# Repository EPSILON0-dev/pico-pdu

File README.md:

# pico-pdu

Power Distribution Unit (PDU) built around the Raspberry Pi **RP2350B** (Pico 2 class MCU).

| | |
|-|-|
|  |  | |

> Status: `v0.1` prototype / work in progress. The firmware won't be finished until the board gets manufactured and tested.

## Features

* 12 channels switched with high-side MOSFETs (8 with current sensing)
* 12 PIO-based UART log collectors, aggregating over USB-CDC
* USB-CDC shell for controlling the switches and log collectors

## Hardware (pcb/)

The board is built around the RP2350B with an external flash chip. The high-side switches are controlled by the MCP23017 I2C GPIO expander. Communication is performed over USB via a USB-C port.

### Current sensing

In the current sensing channels the power is routed via a shunt resistor, whose voltage drop is amplified by the INA4180 and goes to the MCU ADCs.

### Warm Boot

A "warm boot" line is routed from the expander to the MCU; it gets pulled high after the MCU boots up. If the line is high during the MCU boot, it assumes the expander to be the source of truth and reads the GPIO states from it.

### Log Collectors

The 12 log collector channels are routed through resistors and Zener diodes to the MCU and are read with PIO UART RX blocks.

## Firmware (firmware/)

The firmware runs on FreeRTOS using one core. The firmware exposes two USB CDC interfaces **PDU Console** and **Log Collector**.

## PDU Console

For controlling and monitoring the state of the PDU.

## Log Collector (not yet implemented)

Aggregated outputs of each UART. Incoming streams are prefixed with the stream index.

### Console commands

Connect to `PDU Console` at 115200 (e.g. `picocom /dev/ttyACM0`), prompt `pico-pdu> `:

```
help                        Print help
dfu                         Enter the bootloader
relay <on|off> <channel>    Turn on/off relay channel
state                       Human-readable relay + current report
state_raw                   Machine-parseable RELAY/MONITOR dump
log                         Change logger settings (stub)
```

## Build / flash

Requires Pico SDK + ARM toolchain (easiest: Pico VS Code extension, which picks up `pico-vscode.cmake` automatically).

```sh
cd firmware
cmake -B build
cmake --build build
# produces build/pico_pdu.uf2
```

Flash: hold `USB_Boot` + tap `Reset`, copy `pico_pdu.uf2` to the mass-storage device — or run `dfu` from the console (`reset_usb_boot(0,0)`), or use Picotool/OpenOCD via SWD.

## TODOs

- `relay_init/on/off` is in-RAM only, no GPIO/expander wiring.
- `monitor_read_channel_microamps()` returns random data; needs ADC/INA4180 bring-up.
- `cmd_logger` / `LOGGER` output unimplemented.
- `pico_pdu.c` demo only services one RX channel (`piouart0`); multi-channel RX + `NUM_LOGGERS=12` mapping TBD.
- Small bug surface: `send_circular_buffer()` wrap math, `console_command()` extra `\r\n`, `relay` channel bounds message (`0-NUM_RELAYS-1` vs `<=0` check).

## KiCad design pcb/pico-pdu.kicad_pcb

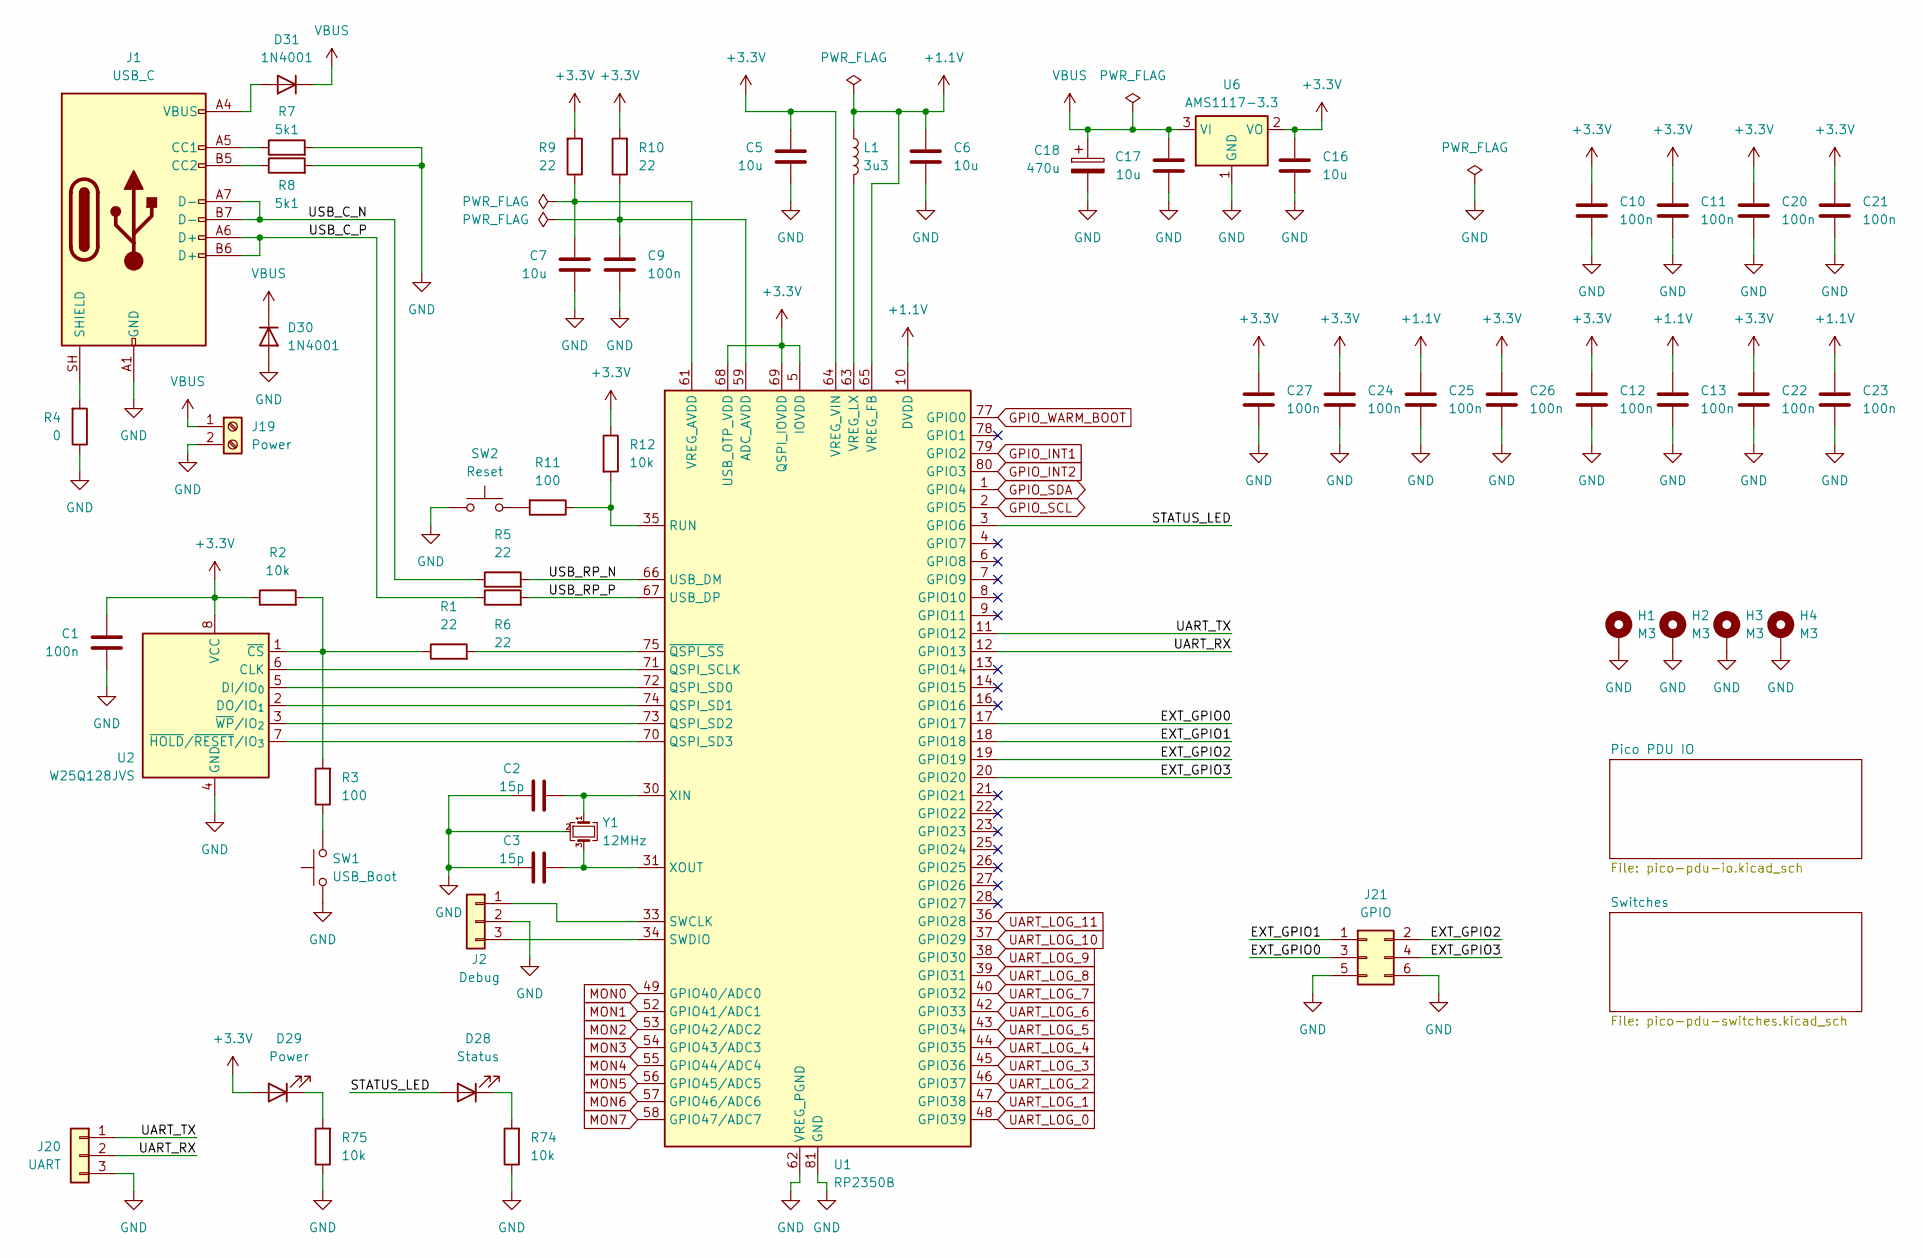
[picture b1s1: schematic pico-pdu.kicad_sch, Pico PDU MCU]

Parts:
C1, C9, C10, C11, C12, C13, C20, C21, C22, C23, C24, C25, C26, C27: 100n; C_0402_1005Metric
C2, C3: 15p; C_0402_1005Metric
C5, C6, C7, C16, C17: 10u; C_0603_1608Metric
C18: 470u; CP_Radial_D10.0mm_P5.00mm
D28: Status; LED_0805_2012Metric
D29: Power; LED_0805_2012Metric
D30, D31: 1N4001; D_DO-41_SOD81_P10.16mm_Horizontal
H1, H2, H3, H4: M3; MountingHole_3.2mm_M3_Pad_Via
J1: USB_C; USB_C_Receptacle_G-Switch_GT-USB-7010ASV
J2: Debug; PinHeader_1x03_P2.54mm_Vertical
J19: Power; TerminalBlock_MaiXu_MX126-5.0-02P_1x02_P5.00mm
J20: UART; PinHeader_1x03_P2.54mm_Vertical
J21: GPIO; PinHeader_2x03_P2.54mm_Vertical
L1: 3u3; L_1008_2520Metric
R1, R5, R6, R9, R10: 22; R_0402_1005Metric
R2, R12, R74, R75: 10k; R_0402_1005Metric
R3, R11: 100; R_0402_1005Metric
R4: 0; R_0402_1005Metric
R7, R8: 5k1; R_0402_1005Metric
SW1: USB_Boot; SW_Push_SPST_NO_Alps_SKRK
SW2: Reset; SW_Push_SPST_NO_Alps_SKRK
U1: RP2350B; QFN-80-1EP_10x10mm_P0.4mm_EP3.4x3.4mm
U2: W25Q128JVS; WSON-8-1EP_6x5mm_P1.27mm_EP3.4x4mm
U6: AMS1117-3.3; SOT-223-3_TabPin2
Y1: 12MHz; Crystal_SMD_2520-4Pin_2.5x2.0mm

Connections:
+1.1V: C6.1, C13.1, C23.1, C25.1, L1.1, U1.10 (DVDD), U1.32 (DVDD), U1.51 (DVDD), U1.65 (VREG_FB)
+3.3V: C1.1, C5.2, C10.1, C11.1, C12.1, C16.1, C20.1, C21.1, C22.1, C24.1, C26.1, C27.1, D29.2 (A), R2.1, R9.2, R10.2, R12.1, U1.5 (IOVDD), U1.15 (IOVDD), U1.24 (IOVDD), U1.29 (IOVDD), U1.41 (IOVDD), U1.50 (IOVDD), U1.60 (IOVDD), U1.64 (VREG_VIN), U1.68 (USB_OTP_VDD), U1.69 (QSPI_IOVDD), U1.76 (IOVDD), U2.8 (VCC), U6.2 (VO); also elsewhere on the board
/EXT_GPIO0: J21.3, U1.17 (GPIO17)
/EXT_GPIO1: J21.1, U1.18 (GPIO18)
/EXT_GPIO2: J21.2, U1.19 (GPIO19)
/EXT_GPIO3: J21.4, U1.20 (GPIO20)
/STATUS_LED: D28.2 (A), U1.3 (GPIO6)
/UART_RX: J20.2, U1.12 (GPIO13)
/UART_TX: J20.1, U1.11 (GPIO12)
/USB_C_N: J1.A7 (D-), J1.B7 (D-), R5.1
/USB_C_P: J1.A6 (D+), J1.B6 (D+), R6.1
/USB_RP_N: R5.2, U1.66 (USB_DM)
/USB_RP_P: R6.2, U1.67 (USB_DP)
GND: C1.2, C2.1, C3.1, C5.1, C6.2, C7.2, C9.2, C10.2, C11.2, C12.2, C13.2, C16.2, C17.2, C18.2, C20.2, C21.2, C22.2, C23.2, C24.2, C25.2, C26.2, C27.2, D30.2 (A), H1.1 (1_1), H2.1 (1_1), H3.1 (1_1), H4.1 (1_1), J1.A1 (GND), J1.A12 (GND), J1.B1 (GND), J1.B12 (GND), J2.2, J19.2, J20.3, J21.5, J21.6, R4.1, R7.2, R8.2, R74.1, R75.1, SW1.1, SW2.2, U1.62 (VREG_PGND), U1.81 (GND), U2.4 (GND), U6.1 (GND), Y1.2 (G), Y1.4 (G); also elsewhere on the board
GPIO_INT1: U1.79 (GPIO2); also elsewhere on the board
GPIO_INT2: U1.80 (GPIO3); also elsewhere on the board
GPIO_SCL: U1.2 (GPIO5); also elsewhere on the board
GPIO_SDA: U1.1 (GPIO4); also elsewhere on the board
GPIO_WARM_BOOT: U1.77 (GPIO0); also elsewhere on the board
MON0: U1.49 (GPIO40/ADC0); also elsewhere on the board
MON1: U1.52 (GPIO41/ADC1); also elsewhere on the board
MON2: U1.53 (GPIO42/ADC2); also elsewhere on the board
MON3: U1.54 (GPIO43/ADC3); also elsewhere on the board
MON4: U1.55 (GPIO44/ADC4); also elsewhere on the board
MON5: U1.56 (GPIO45/ADC5); also elsewhere on the board
MON6: U1.57 (GPIO46/ADC6); also elsewhere on the board
MON7: U1.58 (GPIO47/ADC7); also elsewhere on the board
unnamed: D28.1 (K), R74.2
unnamed: D29.1 (K), R75.2
unnamed: D31.2 (A), J1.A4 (VBUS), J1.A9 (VBUS), J1.B4 (VBUS), J1.B9 (VBUS)
unnamed: J1.A5 (CC1), R7.1
unnamed: J1.B5 (CC2), R8.1
unnamed: J1.SH (SHIELD), R4.2
unnamed: J2.1, U1.33 (SWCLK)
unnamed: J2.3, U1.34 (SWDIO)
unnamed: R3.1, SW1.2
unnamed: R11.2, SW2.1
unnamed: C9.1, R10.1, U1.59 (ADC_AVDD)
unnamed: U1.71 (QSPI_SCLK), U2.6 (CLK)
unnamed: U1.72 (QSPI_SD0), U2.5 (DI/IO_{0})
unnamed: U1.74 (QSPI_SD1), U2.2 (DO/IO_{1})
unnamed: U1.73 (QSPI_SD2), U2.3 (~WP/IO_{2})
unnamed: U1.70 (QSPI_SD3), U2.7 (~HOLD/~RESET/IO_{3})
unnamed: R11.1, R12.2, U1.35 (RUN)
unnamed: C7.1, R9.1, U1.61 (VREG_AVDD)
unnamed: L1.2, U1.63 (VREG_LX)
unnamed: C2.2, U1.30 (XIN), Y1.1
unnamed: C3.2, U1.31 (XOUT), Y1.3
unnamed: R1.2, U1.75 (~QSPI_SS)
unnamed: R1.1, R2.2, R3.2, U2.1 (~CS)
UART_LOG_0: U1.48 (GPIO39); also elsewhere on the board
UART_LOG_1: U1.47 (GPIO38); also elsewhere on the board
UART_LOG_2: U1.46 (GPIO37); also elsewhere on the board
UART_LOG_3: U1.45 (GPIO36); also elsewhere on the board
UART_LOG_4: U1.44 (GPIO35); also elsewhere on the board
UART_LOG_5: U1.43 (GPIO34); also elsewhere on the board
UART_LOG_6: U1.42 (GPIO33); also elsewhere on the board
UART_LOG_7: U1.40 (GPIO32); also elsewhere on the board
UART_LOG_8: U1.39 (GPIO31); also elsewhere on the board
UART_LOG_9: U1.38 (GPIO30); also elsewhere on the board
UART_LOG_10: U1.37 (GPIO29); also elsewhere on the board
UART_LOG_11: U1.36 (GPIO28); also elsewhere on the board
VBUS: C17.1, C18.1, D30.1 (K), D31.1 (K), J19.1, U6.3 (VI)

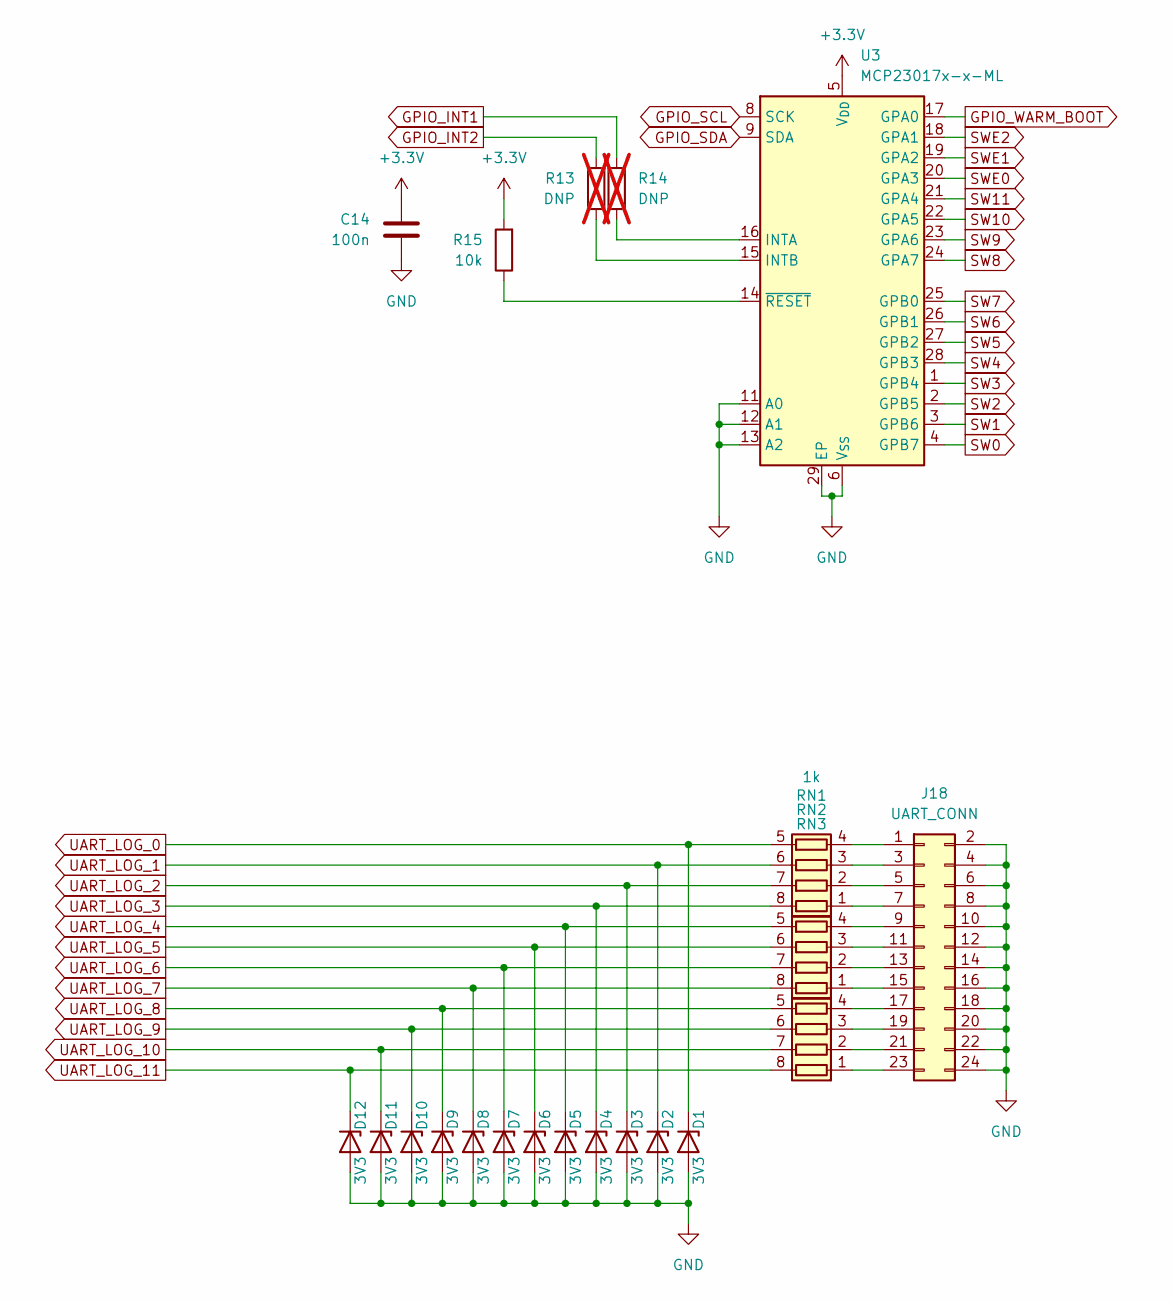
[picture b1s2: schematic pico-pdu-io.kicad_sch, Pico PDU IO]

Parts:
C14: 100n; C_0402_1005Metric
D1, D2, D3, D4, D5, D6, D7, D8, D9, D10, D11, D12: 3V3; D_MicroMELF
J18: UART_CONN; PinHeader_2x12_P2.54mm_Vertical
R13, R14: DNP; R_0402_1005Metric; not fitted
R15: 10k; R_0402_1005Metric
RN1, RN2, RN3: 1k; R_Array_Concave_4x0402
U3: MCP23017x-x-ML; QFN-28-1EP_6x6mm_P0.65mm_EP4.25x4.25mm

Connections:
+3.3V: C14.1, R15.2, U3.5 (V_{DD}); also elsewhere on the board
GND: C14.2, D1.2 (A), D2.2 (A), D3.2 (A), D4.2 (A), D5.2 (A), D6.2 (A), D7.2 (A), D8.2 (A), D9.2 (A), D10.2 (A), D11.2 (A), D12.2 (A), J18.2, J18.4, J18.6, J18.8, J18.10, J18.12, J18.14, J18.16, J18.18, J18.20, J18.22, J18.24, U3.6 (V_{SS}), U3.11 (A0), U3.12 (A1), U3.13 (A2), U3.29 (EP); also elsewhere on the board
GPIO_INT1: R14.2; also elsewhere on the board
GPIO_INT2: R13.2; also elsewhere on the board
GPIO_SCL: U3.8 (SCK); also elsewhere on the board
GPIO_SDA: U3.9 (SDA); also elsewhere on the board
GPIO_WARM_BOOT: U3.17 (GPA0); also elsewhere on the board
unnamed: J18.1, RN1.4 (R4.1)
unnamed: J18.3, RN1.3 (R3.1)
unnamed: J18.5, RN1.2 (R2.1)
unnamed: J18.7, RN1.1 (R1.1)
unnamed: J18.9, RN2.4 (R4.1)
unnamed: J18.11, RN2.3 (R3.1)
unnamed: J18.13, RN2.2 (R2.1)
unnamed: J18.15, RN2.1 (R1.1)
unnamed: J18.17, RN3.4 (R4.1)
unnamed: J18.19, RN3.3 (R3.1)
unnamed: J18.21, RN3.2 (R2.1)
unnamed: J18.23, RN3.1 (R1.1)
unnamed: R14.1, U3.16 (INTA)
unnamed: R13.1, U3.15 (INTB)
unnamed: R15.1, U3.14 (~RESET)
SW0: U3.4 (GPB7); also elsewhere on the board
SW1: U3.3 (GPB6); also elsewhere on the board
SW2: U3.2 (GPB5); also elsewhere on the board
SW3: U3.1 (GPB4); also elsewhere on the board
SW4: U3.28 (GPB3); also elsewhere on the board
SW5: U3.27 (GPB2); also elsewhere on the board
SW6: U3.26 (GPB1); also elsewhere on the board
SW7: U3.25 (GPB0); also elsewhere on the board
SW8: U3.24 (GPA7); also elsewhere on the board
SW9: U3.23 (GPA6); also elsewhere on the board
SW10: U3.22 (GPA5); also elsewhere on the board
SW11: U3.21 (GPA4); also elsewhere on the board
SWE0: U3.20 (GPA3); also elsewhere on the board
SWE1: U3.19 (GPA2); also elsewhere on the board
SWE2: U3.18 (GPA1); also elsewhere on the board
UART_LOG_0: D1.1 (K), RN1.5 (R4.2); also elsewhere on the board
UART_LOG_1: D2.1 (K), RN1.6 (R3.2); also elsewhere on the board
UART_LOG_2: D3.1 (K), RN1.7 (R2.2); also elsewhere on the board
UART_LOG_3: D4.1 (K), RN1.8 (R1.2); also elsewhere on the board
UART_LOG_4: D5.1 (K), RN2.5 (R4.2); also elsewhere on the board
UART_LOG_5: D6.1 (K), RN2.6 (R3.2); also elsewhere on the board
UART_LOG_6: D7.1 (K), RN2.7 (R2.2); also elsewhere on the board
UART_LOG_7: D8.1 (K), RN2.8 (R1.2); also elsewhere on the board
UART_LOG_8: D9.1 (K), RN3.5 (R4.2); also elsewhere on the board
UART_LOG_9: D10.1 (K), RN3.6 (R3.2); also elsewhere on the board
UART_LOG_10: D11.1 (K), RN3.7 (R2.2); also elsewhere on the board
UART_LOG_11: D12.1 (K), RN3.8 (R1.2); also elsewhere on the board

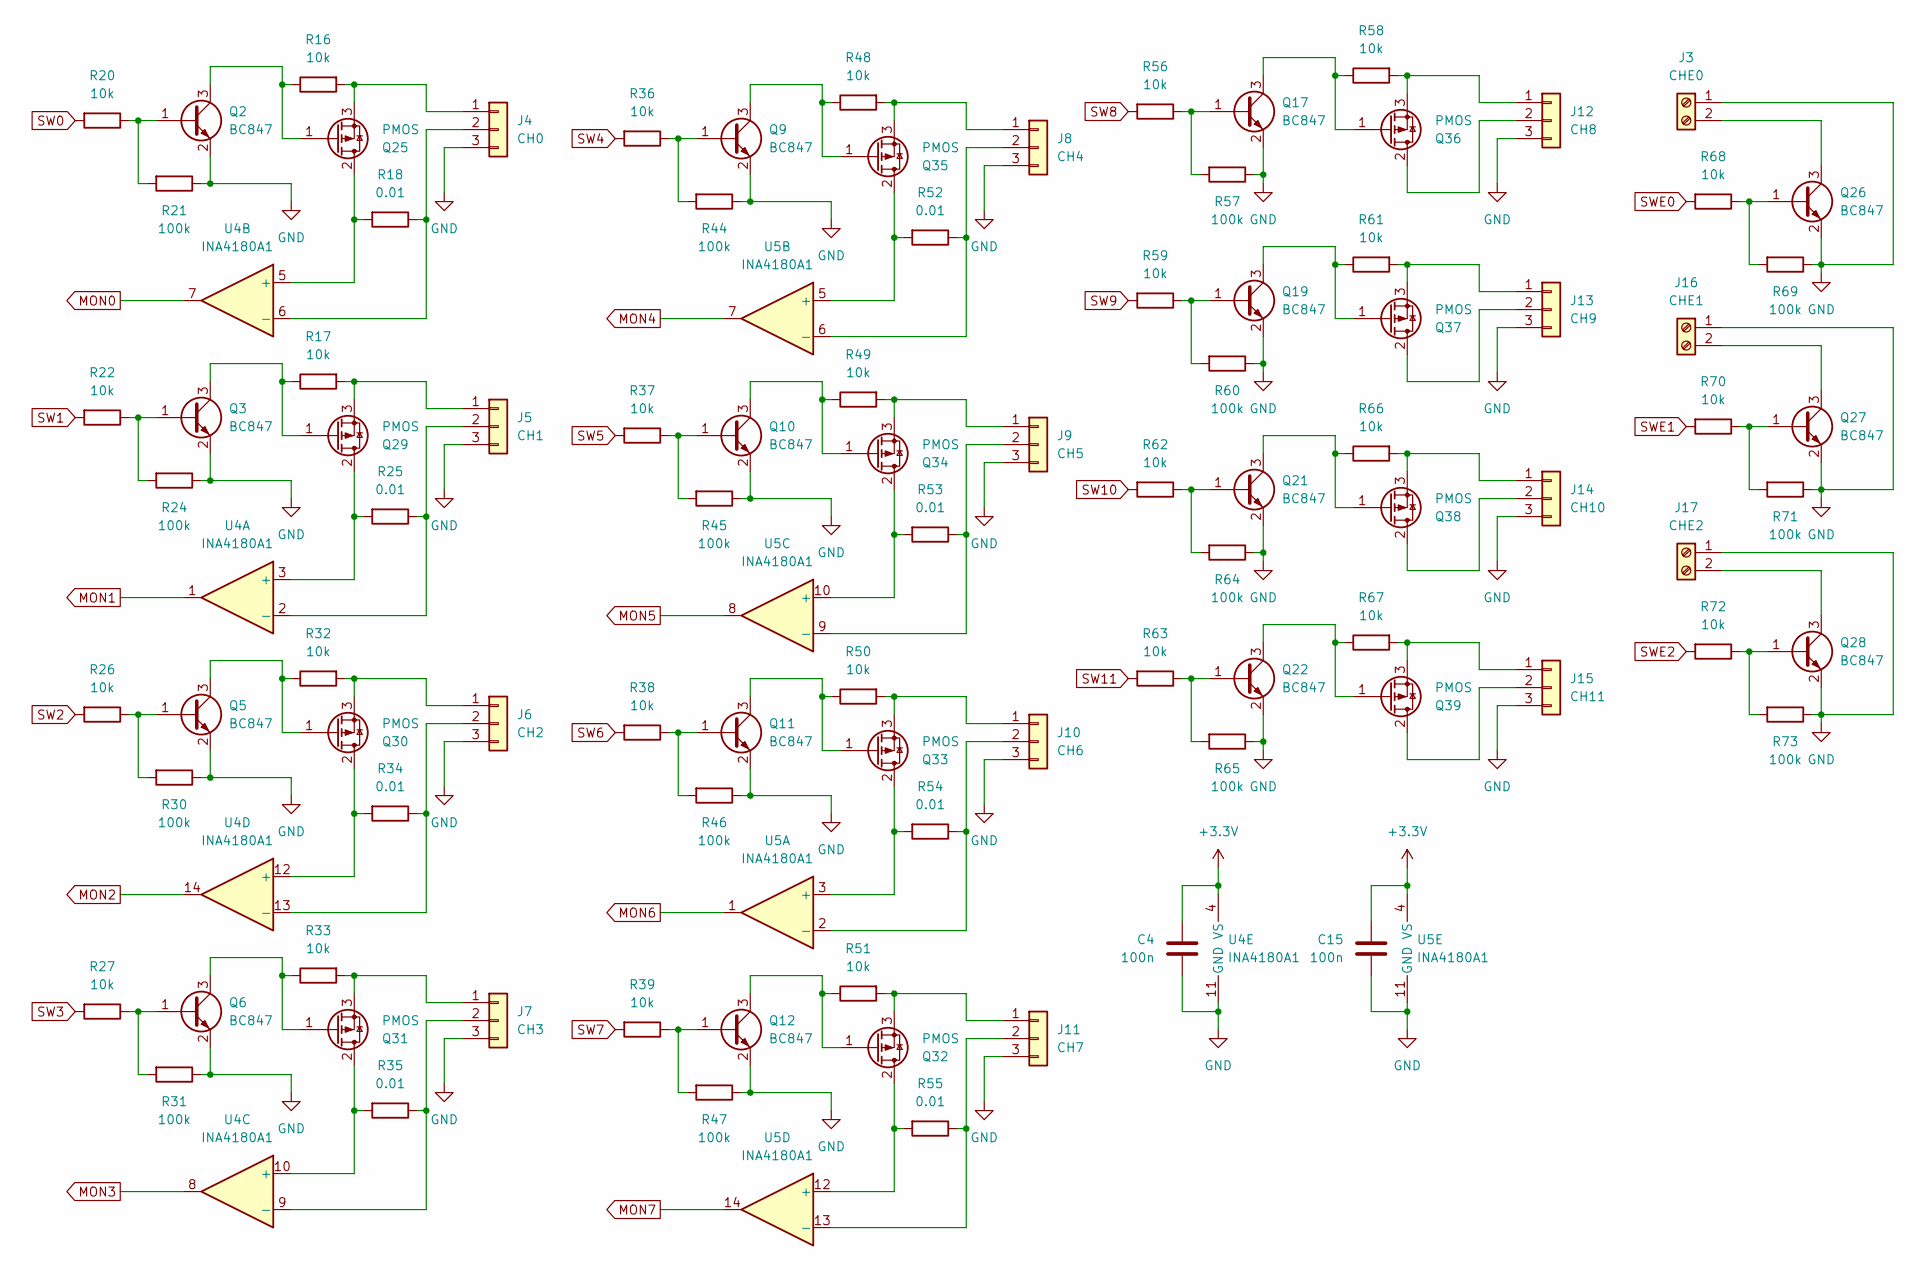
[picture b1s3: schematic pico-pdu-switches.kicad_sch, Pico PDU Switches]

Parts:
C4, C15: 100n; C_0402_1005Metric
J3: CHE0; TerminalBlock_MaiXu_MX126-5.0-02P_1x02_P5.00mm
J4: CH0; TerminalBlock_MaiXu_MX126-5.0-03P_1x03_P5.00mm
J5: CH1; TerminalBlock_MaiXu_MX126-5.0-03P_1x03_P5.00mm
J6: CH2; TerminalBlock_MaiXu_MX126-5.0-03P_1x03_P5.00mm
J7: CH3; TerminalBlock_MaiXu_MX126-5.0-03P_1x03_P5.00mm
J8: CH4; TerminalBlock_MaiXu_MX126-5.0-03P_1x03_P5.00mm
J9: CH5; TerminalBlock_MaiXu_MX126-5.0-03P_1x03_P5.00mm
J10: CH6; TerminalBlock_MaiXu_MX126-5.0-03P_1x03_P5.00mm
J11: CH7; TerminalBlock_MaiXu_MX126-5.0-03P_1x03_P5.00mm
J12: CH8; TerminalBlock_MaiXu_MX126-5.0-03P_1x03_P5.00mm
J13: CH9; TerminalBlock_MaiXu_MX126-5.0-03P_1x03_P5.00mm
J14: CH10; TerminalBlock_MaiXu_MX126-5.0-03P_1x03_P5.00mm
J15: CH11; TerminalBlock_MaiXu_MX126-5.0-03P_1x03_P5.00mm
J16: CHE1; TerminalBlock_MaiXu_MX126-5.0-02P_1x02_P5.00mm
J17: CHE2; TerminalBlock_MaiXu_MX126-5.0-02P_1x02_P5.00mm
Q2, Q3, Q5, Q6, Q9, Q10, Q11, Q12, Q17, Q19, Q21, Q22, Q26, Q27, Q28: BC847; SOT-23
Q25, Q29, Q30, Q31, Q32, Q33, Q34, Q35, Q36, Q37, Q38, Q39: PMOS; TO-252-3_TabPin2
R16, R17, R20, R22, R26, R27, R32, R33, R36, R37, R38, R39, R48, R49, R50, R51, R56, R58, R59, R61, R62, R63, R66, R67, R68, R70, R72: 10k; R_0402_1005Metric
R18, R25, R34, R35, R52, R53, R54, R55: 0.01; R_2512_6332Metric
R21, R24, R30, R31, R44, R45, R46, R47, R57, R60, R64, R65, R69, R71, R73: 100k; R_0402_1005Metric
U4, U5: INA4180A1; TSSOP-14_4.4x5mm_P0.65mm

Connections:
+3.3V: C4.1, C15.1, U4.4 (VS), U5.4 (VS); also elsewhere on the board
GND: C4.2, C15.2, J3.1, J4.3, J5.3, J6.3, J7.3, J8.3, J9.3, J10.3, J11.3, J12.3, J13.3, J14.3, J15.3, J16.1, J17.1, Q2.2 (E), Q3.2 (E), Q5.2 (E), Q6.2 (E), Q9.2 (E), Q10.2 (E), Q11.2 (E), Q12.2 (E), Q17.2 (E), Q19.2 (E), Q21.2 (E), Q22.2 (E), Q26.2 (E), Q27.2 (E), Q28.2 (E), R21.1, R24.1, R30.1, R31.1, R44.1, R45.1, R46.1, R47.1, R57.1, R60.1, R64.1, R65.1, R69.1, R71.1, R73.1, U4.11 (GND), U5.11 (GND); also elsewhere on the board
MON0: U4.7; also elsewhere on the board
MON1: U4.1; also elsewhere on the board
MON2: U4.14; also elsewhere on the board
MON3: U4.8; also elsewhere on the board
MON4: U5.7; also elsewhere on the board
MON5: U5.8; also elsewhere on the board
MON6: U5.1; also elsewhere on the board
MON7: U5.14; also elsewhere on the board
unnamed: J3.2, Q26.3 (C)
unnamed: J4.1, Q25.3 (S), R16.2
unnamed: J4.2, R18.1, U4.6 (-)
unnamed: J5.1, Q29.3 (S), R17.2
unnamed: J5.2, R25.1, U4.2 (-)
unnamed: J6.1, Q30.3 (S), R32.2
unnamed: J6.2, R34.1, U4.13 (-)
unnamed: J7.1, Q31.3 (S), R33.2
unnamed: J7.2, R35.1, U4.9 (-)
unnamed: J8.1, Q35.3 (S), R48.2
unnamed: J8.2, R52.1, U5.6 (-)
unnamed: J9.1, Q34.3 (S), R49.2
unnamed: J9.2, R53.1, U5.9 (-)
unnamed: J10.1, Q33.3 (S), R50.2
unnamed: J10.2, R54.1, U5.2 (-)
unnamed: J11.1, Q32.3 (S), R51.2
unnamed: J11.2, R55.1, U5.13 (-)
unnamed: J12.1, Q36.3 (S), R58.2
unnamed: J12.2, Q36.2 (D)
unnamed: J13.1, Q37.3 (S), R61.2
unnamed: J13.2, Q37.2 (D)
unnamed: J14.1, Q38.3 (S), R66.2
unnamed: J14.2, Q38.2 (D)
unnamed: J15.1, Q39.3 (S), R67.2
unnamed: J15.2, Q39.2 (D)
unnamed: J16.2, Q27.3 (C)
unnamed: J17.2, Q28.3 (C)
unnamed: Q2.1 (B), R20.1, R21.2
unnamed: Q2.3 (C), Q25.1 (G), R16.1
unnamed: Q3.1 (B), R22.1, R24.2
unnamed: Q5.1 (B), R26.1, R30.2
unnamed: Q6.1 (B), R27.1, R31.2
unnamed: Q9.1 (B), R36.1, R44.2
unnamed: Q10.1 (B), R37.1, R45.2
unnamed: Q10.3 (C), Q34.1 (G), R49.1
unnamed: Q11.1 (B), R38.1, R46.2
unnamed: Q11.3 (C), Q33.1 (G), R50.1
unnamed: Q12.1 (B), R39.1, R47.2
unnamed: Q12.3 (C), Q32.1 (G), R51.1
unnamed: Q17.1 (B), R56.1, R57.2
unnamed: Q17.3 (C), Q36.1 (G), R58.1
unnamed: Q19.1 (B), R59.1, R60.2
unnamed: Q19.3 (C), Q37.1 (G), R61.1
unnamed: Q21.1 (B), R62.1, R64.2
unnamed: Q21.3 (C), Q38.1 (G), R66.1
unnamed: Q22.1 (B), R63.1, R65.2
unnamed: Q22.3 (C), Q39.1 (G), R67.1
unnamed: Q25.2 (D), R18.2, U4.5 (+)
unnamed: Q26.1 (B), R68.1, R69.2
unnamed: Q27.1 (B), R70.1, R71.2
unnamed: Q28.1 (B), R72.1, R73.2
unnamed: Q29.2 (D), R25.2, U4.3 (+)
unnamed: Q3.3 (C), Q29.1 (G), R17.1
unnamed: Q30.2 (D), R34.2, U4.12 (+)
unnamed: Q5.3 (C), Q30.1 (G), R32.1
unnamed: Q31.2 (D), R35.2, U4.10 (+)
unnamed: Q6.3 (C), Q31.1 (G), R33.1
unnamed: Q32.2 (D), R55.2, U5.12 (+)
unnamed: Q33.2 (D), R54.2, U5.3 (+)
unnamed: Q34.2 (D), R53.2, U5.10 (+)
unnamed: Q35.2 (D), R52.2, U5.5 (+)
unnamed: Q9.3 (C), Q35.1 (G), R48.1
SW0: R20.2; also elsewhere on the board
SW1: R22.2; also elsewhere on the board
SW2: R26.2; also elsewhere on the board
SW3: R27.2; also elsewhere on the board
SW4: R36.2; also elsewhere on the board
SW5: R37.2; also elsewhere on the board
SW6: R38.2; also elsewhere on the board
SW7: R39.2; also elsewhere on the board
SW8: R56.2; also elsewhere on the board
SW9: R59.2; also elsewhere on the board
SW10: R62.2; also elsewhere on the board
SW11: R63.2; also elsewhere on the board
SWE0: R68.2; also elsewhere on the board
SWE1: R70.2; also elsewhere on the board
SWE2: R72.2; also elsewhere on the board

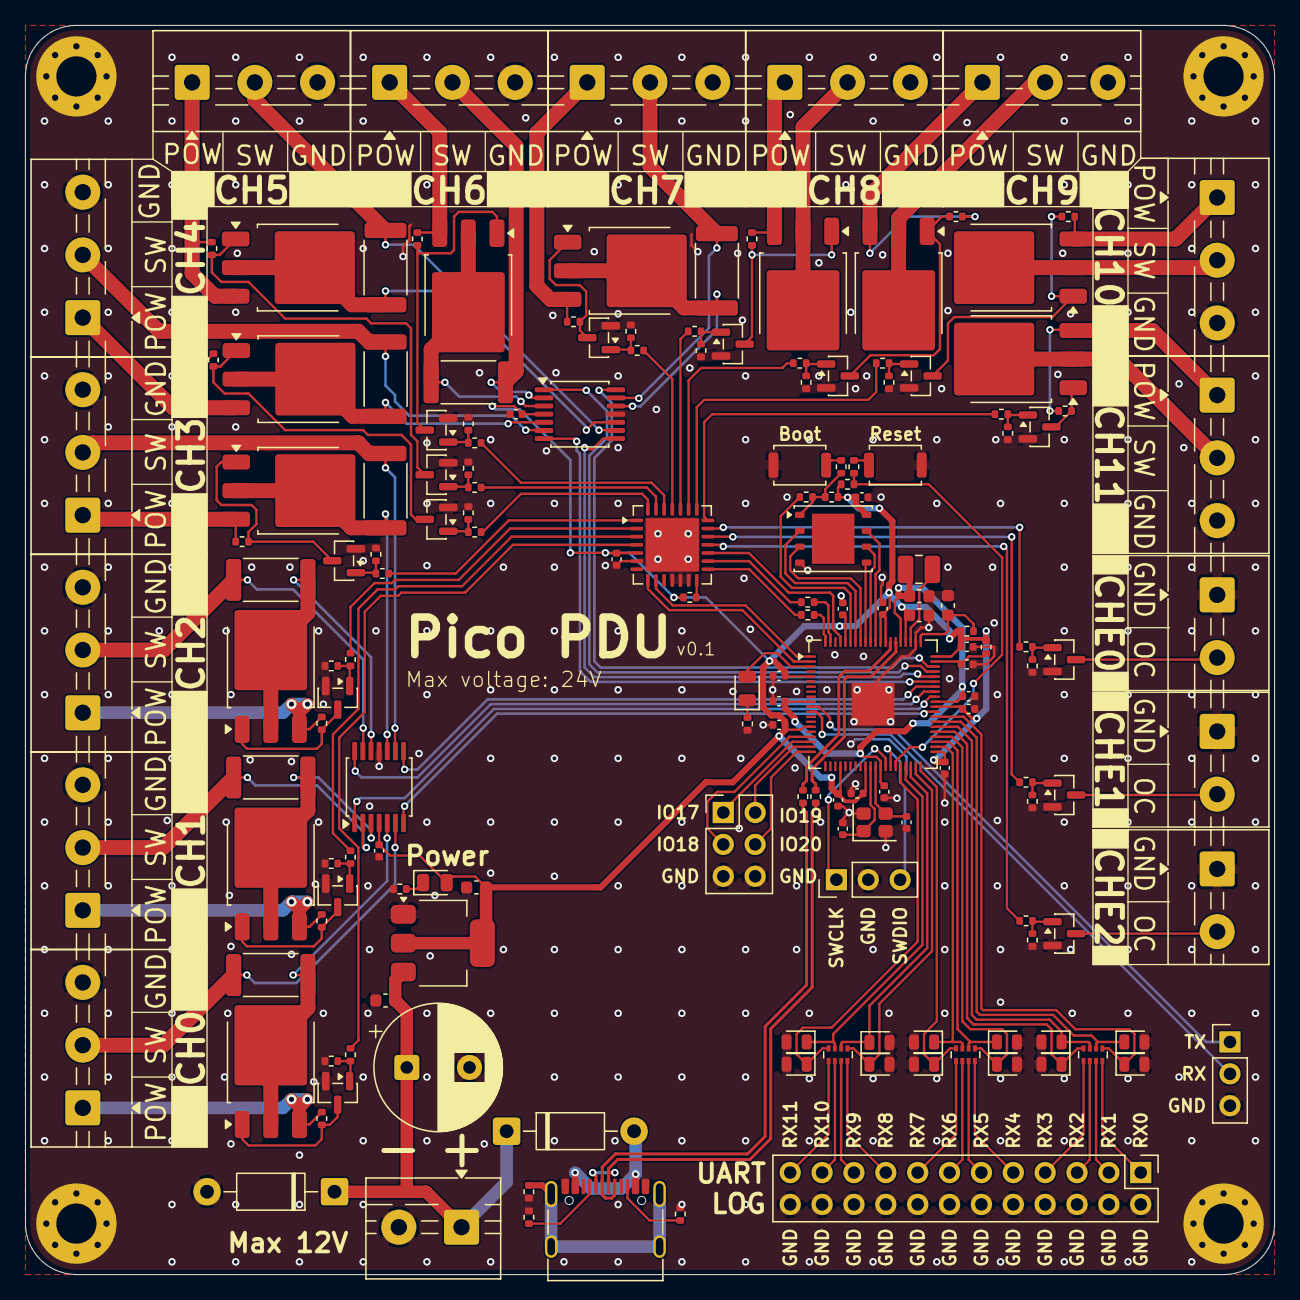
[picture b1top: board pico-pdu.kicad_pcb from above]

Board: 2 copper layers, 99.6 x 99.6 mm, 173 parts (0 on the bottom side), 155 nets.
